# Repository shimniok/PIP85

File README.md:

# PIP85
Put-In-Project ATtiny85 with signal/vcc/gnd for each pin, onboard regulator and more.

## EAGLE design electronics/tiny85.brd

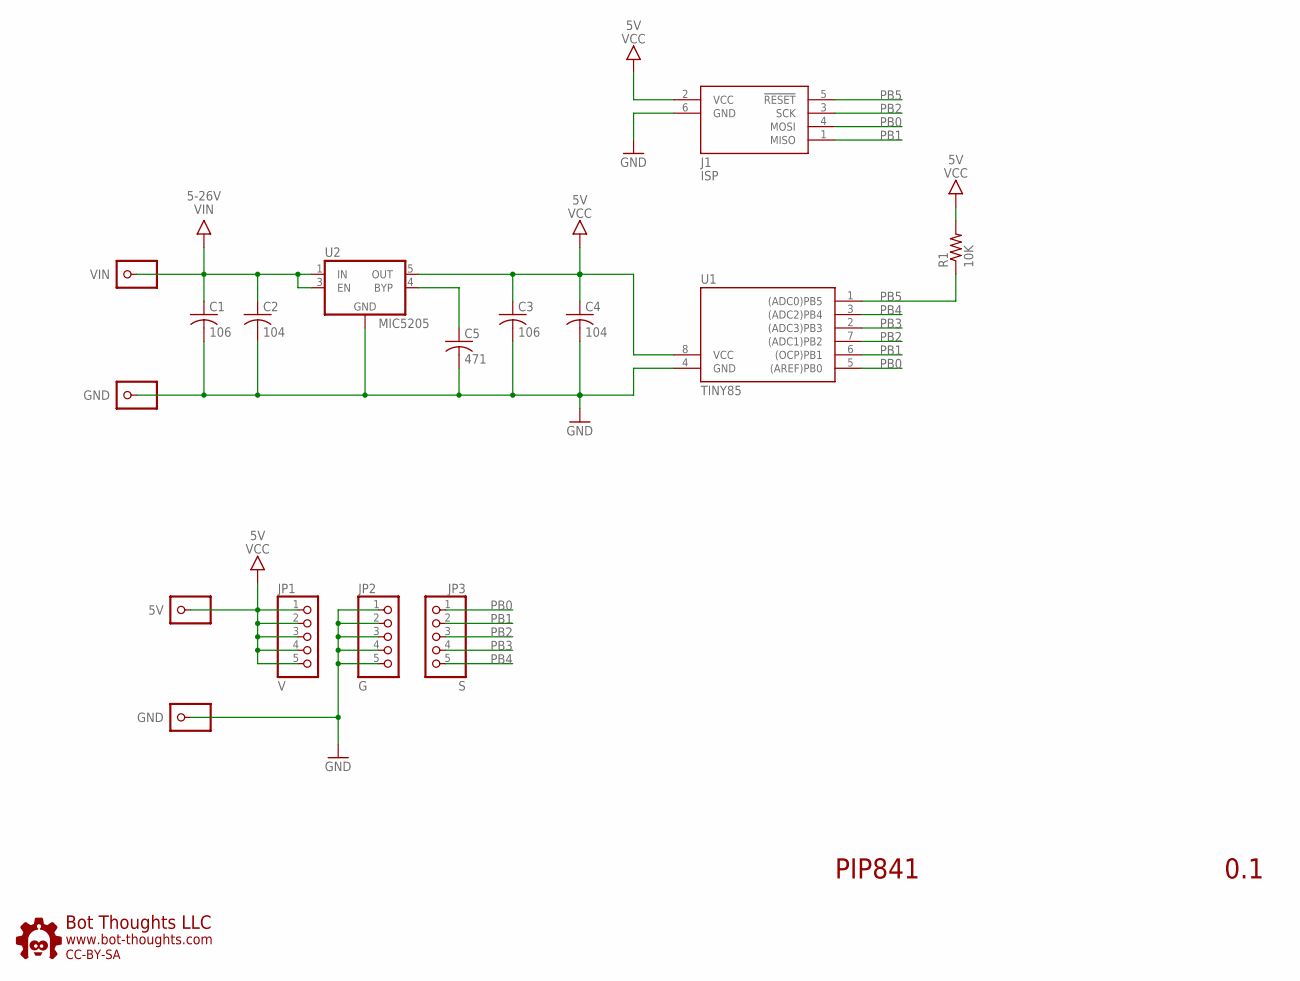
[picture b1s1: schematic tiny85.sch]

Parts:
C1, C3: 106; 1206
C2, C4: 104; 0603
C5: 471; 0603
J1: ISP; CON6P2R
JP1: V; 1X05-S
JP2: G; 1X05-S
JP3: S; 1X05-S
JP4, JP6: GND; 1X01
JP5: VIN; 1X01
JP8: 5V; 1X01
R1: 10K; 0603
U1: TINY85; SOIC8
U2: MIC5205; SOT23-5
U$3: BTLOGO-LOGO-MD; BTLOGOM

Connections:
GND: C1.2 (-), C2.2 (-), C3.2 (-), C4.2 (-), C5.2 (-), J1.6 (GND), JP2.1, JP2.2, JP2.3, JP2.4, JP2.5, JP4.1, JP6.1, U1.4 (GND), U2.2 (GND)
unnamed: C5.1 (+), U2.4 (BYP)
PB0: J1.4 (MOSI), JP3.1, U1.5 ((AREF)PB0)
PB1: J1.1 (MISO), JP3.2, U1.6 ((OCP)PB1)
PB2: J1.3 (SCK), JP3.3, U1.7 ((ADC1)PB2)
PB3: JP3.4, U1.2 ((ADC3)PB3)
PB4: JP3.5, U1.3 ((ADC2)PB4)
PB5: J1.5 (!RESET), R1.1, U1.1 ((ADC0)PB5)
VCC: C3.1 (+), C4.1 (+), J1.2 (VCC), JP1.1, JP1.2, JP1.3, JP1.4, JP1.5, JP8.1, R1.2, U1.8 (VCC), U2.5 (OUT)
VIN: C1.1 (+), C2.1 (+), JP5.1, U2.1 (IN), U2.3 (EN)

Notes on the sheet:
PIP841
0.1

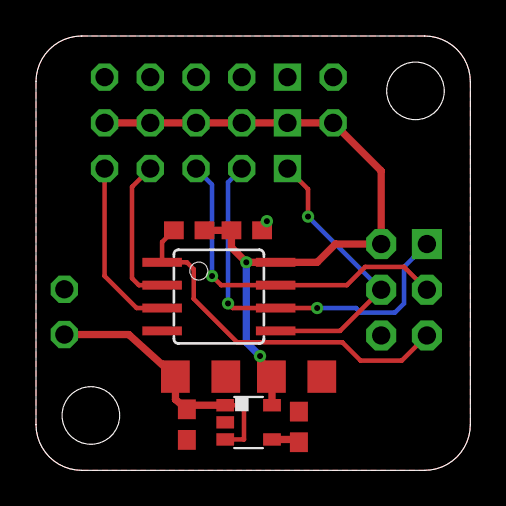
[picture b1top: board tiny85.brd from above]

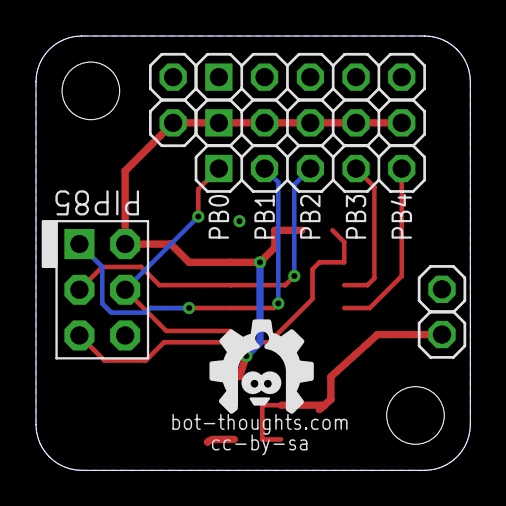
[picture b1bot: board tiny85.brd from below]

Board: 2 copper layers, 24.1 x 24.1 mm, 17 parts (9 on the bottom side), 10 nets.

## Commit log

2017-06-12 initial version
2021-02-10 added description

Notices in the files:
electronics/tiny85.brd:
cc-by-sa
